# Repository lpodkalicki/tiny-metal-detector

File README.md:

# Tiny Metal Detector
ATtiny13 based PI (Pulse Induction) Metal Detector

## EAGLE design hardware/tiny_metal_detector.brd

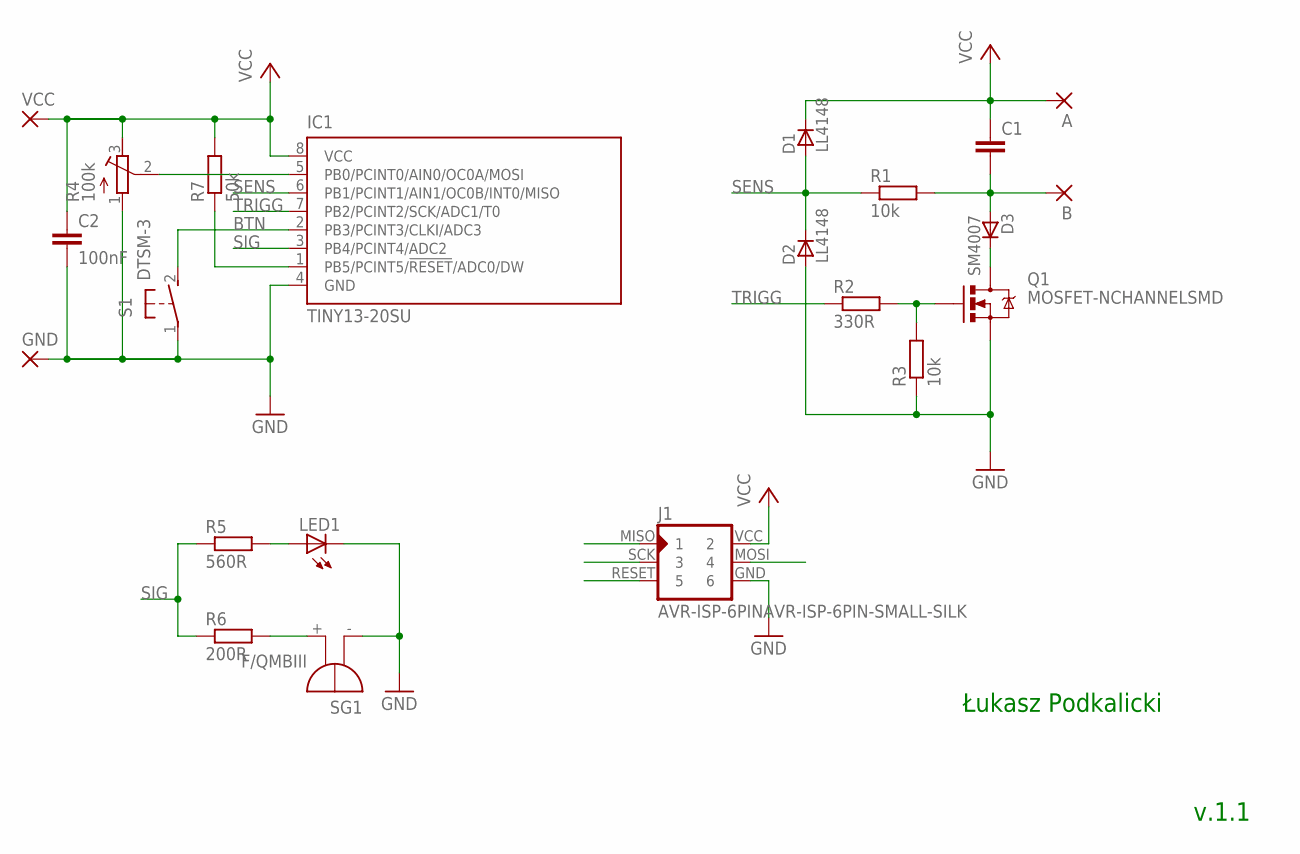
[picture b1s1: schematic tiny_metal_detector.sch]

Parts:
A: 3,17/1,1
B: 3,17/1,1
C1: C-EUC1206K; C1206K
C2: 100nF; C1206K
D1, D2: LL4148; SOD80_DO213AA_MINIMELF
D3: SM4007; MELF-MLL41_DO213AB
GND: 3,17/1,1
IC1: TINY13-20SU; 8S2
J1: AVR-ISP-6PINAVR-ISP-6PIN-SMALL-SILK; AVR-ISP-6PIN-SMAILL-SILK
LED1: LEDCHIPLED_1206; CHIPLED_1206
Q1: MOSFET-NCHANNELSMD; SOT23-3
R1, R3: 10k; R1206
R2: 330R; R1206
R4: 100k; RTRIM3296W
R5: 560R; R1206
R6: 200R; R1206
R7: 50k; R1206
S1: DTSM-3
SG1: F/QMBIII
VCC: 3,17/1,1

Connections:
BTN: IC1.2 (PB3/PCINT3/CLKI/ADC3), S1.2
GND: C2.2, D2.A, GND.1, IC1.4 (GND), J1.GND (6), LED1.C, Q1.2 (S), R3.1, R4.1 (A), S1.1, SG1.- (+)
MOSI: IC1.5 (PB0/PCINT0/AIN0/OC0A/MOSI), J1.MOSI (4), R4.2 (S)
unnamed: R6.2, SG1.+ (-)
unnamed: B.1, C1.2, D3.A, R1.2
unnamed: D3.C, Q1.3 (D)
unnamed: Q1.1 (G), R2.2, R3.2
unnamed: LED1.A, R5.2
RESET: IC1.1 (PB5/PCINT5/!RESET!/ADC0/DW), J1.RESET (5), R7.1
SENS: D1.A, D2.C, IC1.6 (PB1/PCINT1/AIN1/OC0B/INT0/MISO), J1.MISO (1), R1.1
SIG: IC1.3 (PB4/PCINT4/ADC2), R5.1, R6.1
TRIGG: IC1.7 (PB2/PCINT2/SCK/ADC1/T0), J1.SCK (3), R2.1
VCC: A.1, C1.1, C2.1, D1.C, IC1.8 (VCC), J1.VCC (2), R4.3 (E), R7.2, VCC.1

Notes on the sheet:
Łukasz Podkalicki
v.1.1

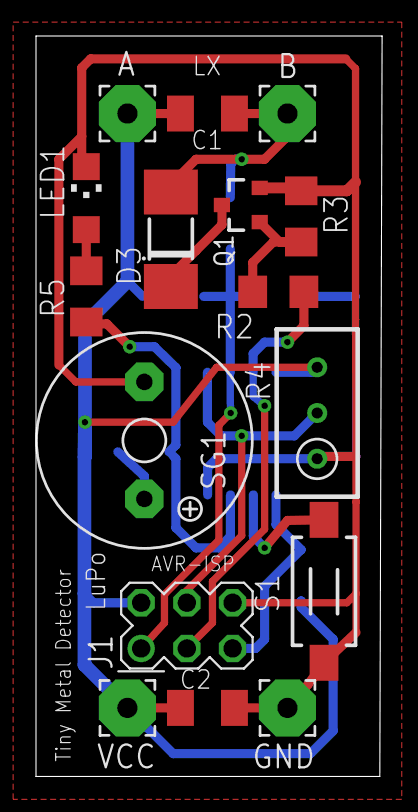
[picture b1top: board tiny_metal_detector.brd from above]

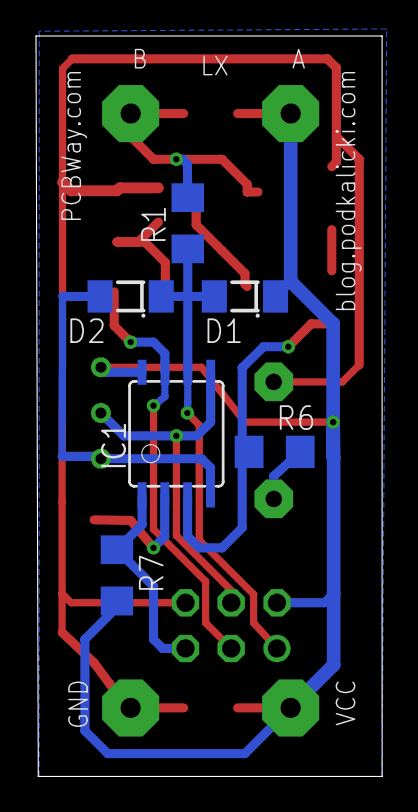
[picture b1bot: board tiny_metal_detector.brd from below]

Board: 2 copper layers, 19.2 x 41.1 mm, 22 parts (6 on the bottom side), 13 nets.

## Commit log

2019-03-09 Add software.
2019-03-09 Add empty schematic.
2019-03-09 Update README.
2019-03-14 Add updated schematic, brd, gerber files and board images.
2020-12-10 Adding hex-file.
2022-04-09 -c switch added
